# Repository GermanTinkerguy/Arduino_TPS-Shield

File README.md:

**Functions**

- Full functional circuit for a TPS/MyCo Arduino Shield based on the layout from [https://wkla.no-ip.biz](https://wkla.no-ip.biz/ArduinoWiki/doku.php?id=arduino:arduinosps)

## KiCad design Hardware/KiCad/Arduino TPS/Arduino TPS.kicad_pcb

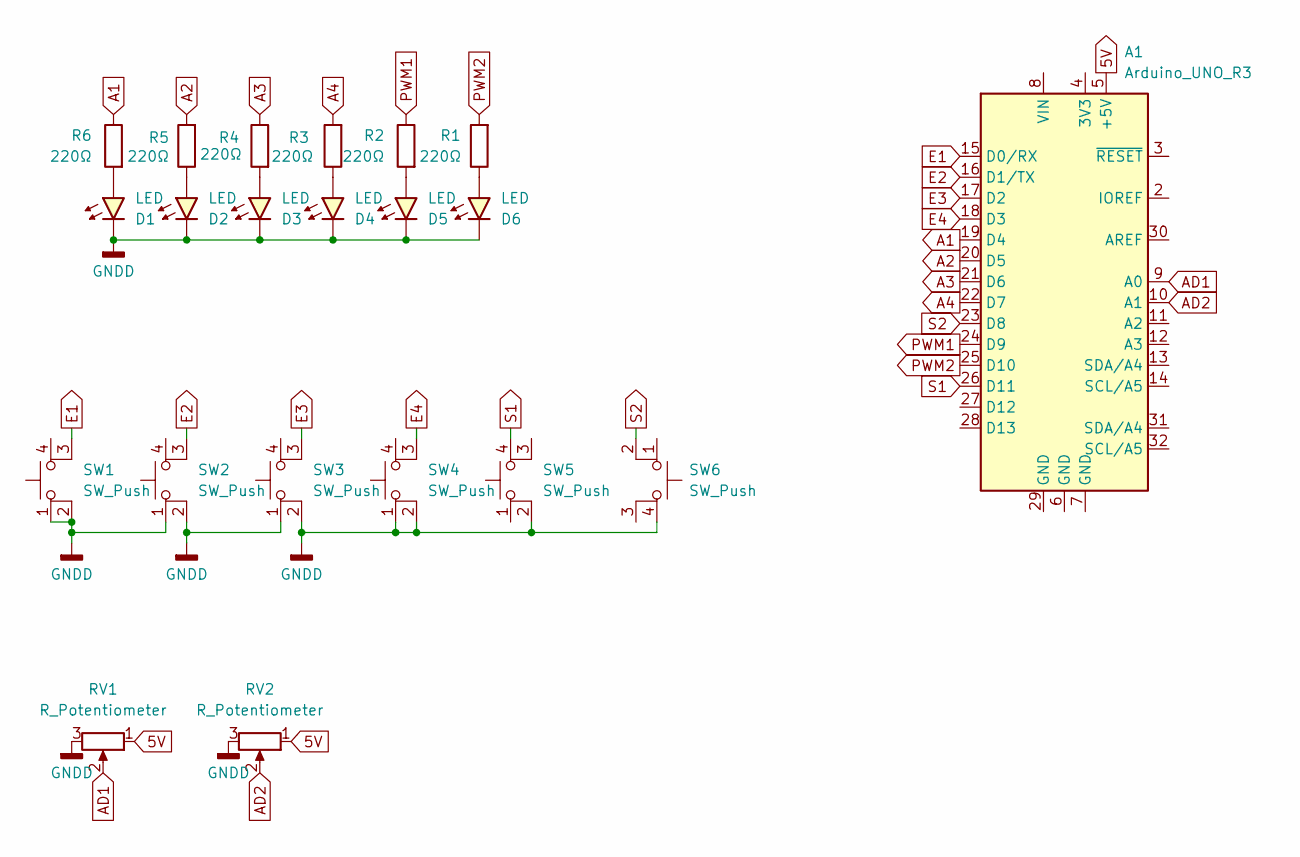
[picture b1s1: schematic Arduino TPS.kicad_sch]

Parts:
A1: Arduino_UNO_R3
D1, D2, D3, D4, D5, D6: LED; LED_D3.0mm
R1, R2, R3, R4, R5, R6: 220Ω; R_Axial_DIN0207_L6.3mm_D2.5mm_P5.08mm_Vertical
RV1, RV2: R_Potentiometer; 3310
SW1, SW2, SW3, SW4, SW5, SW6: SW_Push; SW_PUSH_6mm

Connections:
5V: A1.5 (+5V), RV1.1, RV2.1
A1: A1.19 (D4), R6.1
A2: A1.20 (D5), R5.2
A3: A1.21 (D6), R4.1
A4: A1.22 (D7), R3.2
AD1: A1.9 (A0), RV1.2
AD2: A1.10 (A1), RV2.2
E1: A1.15 (D0/RX), SW1.3 (K)
E2: A1.16 (D1/TX), SW2.3 (K)
E3: A1.17 (D2), SW3.3 (K)
E4: A1.18 (D3), SW4.3 (K)
GNDD: D1.1 (K), D2.1 (K), D3.1 (K), D4.1 (K), D5.1 (K), D6.1 (K), RV1.3, RV2.3, SW1.1, SW1.2, SW2.1, SW2.2, SW3.1, SW3.2, SW4.1, SW4.2, SW5.2, SW6.4 (A)
unnamed: D1.2 (A), R6.2
unnamed: D2.2 (A), R5.1
unnamed: D3.2 (A), R4.2
unnamed: D4.2 (A), R3.1
unnamed: D5.2 (A), R2.2
unnamed: D6.2 (A), R1.1
PWM1: A1.24 (D9), R2.1
PWM2: A1.25 (D10), R1.2
S1: A1.26 (D11), SW5.4 (A)
S2: A1.23 (D8), SW6.2

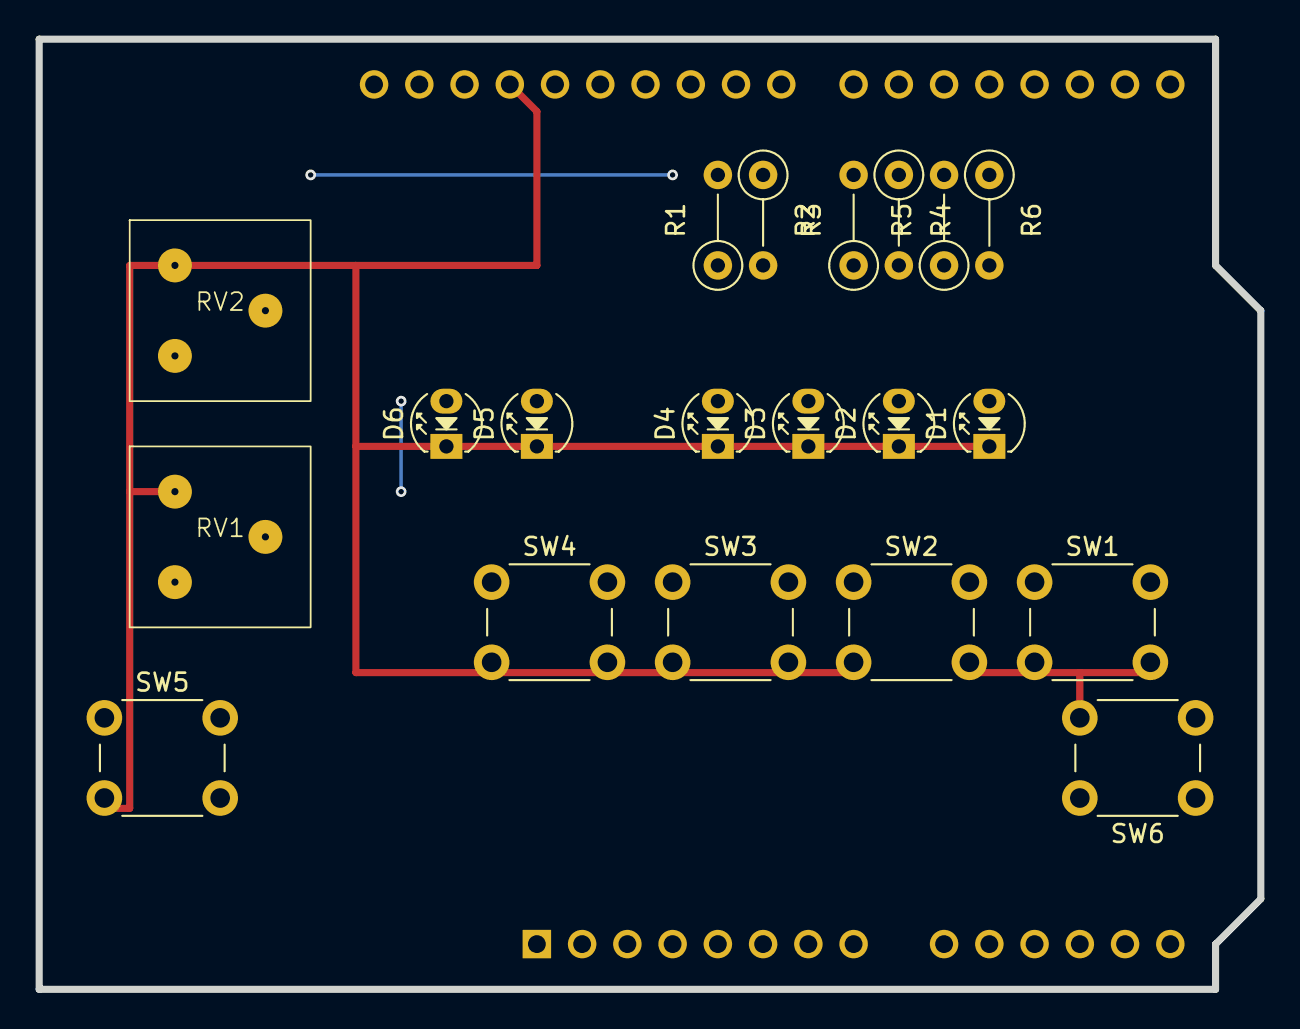
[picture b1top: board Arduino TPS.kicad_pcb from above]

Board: 10 copper layers, 68.6 x 53.3 mm, 21 parts (1 on the bottom side), 22 nets.

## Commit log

2024-11-21 Rename TPS Shield (Perfboard).diy to Hardware/DIY Layout Creator/TPS Shield (Perfboard).diy
2024-12-17 Update - Function fully tested - README.md update
2025-01-09 Delete Docs/lernpaket.pdf
    Update
    - Unneccesary
